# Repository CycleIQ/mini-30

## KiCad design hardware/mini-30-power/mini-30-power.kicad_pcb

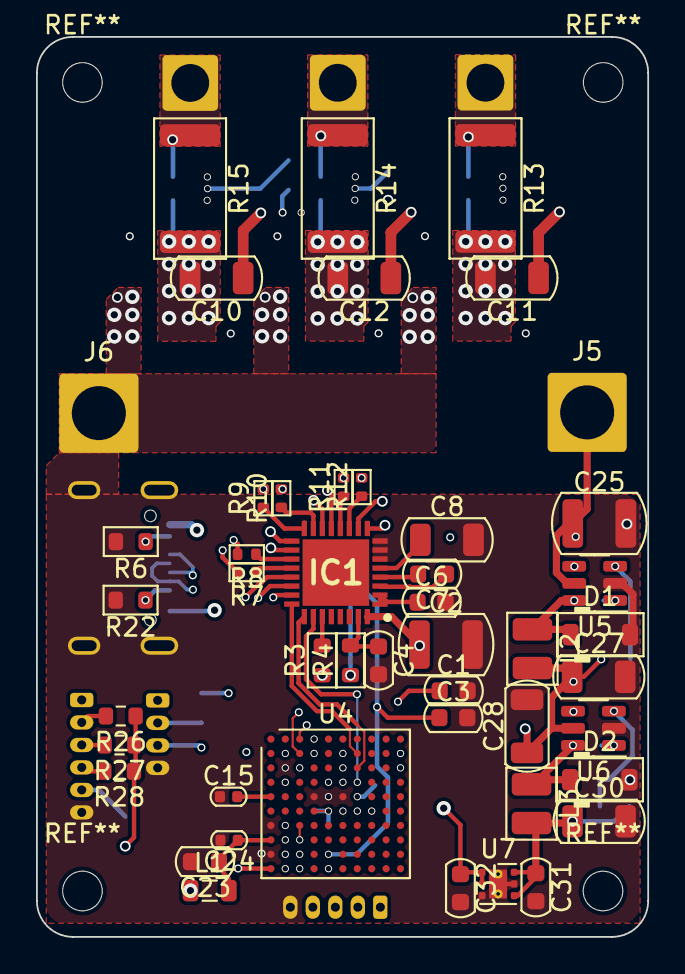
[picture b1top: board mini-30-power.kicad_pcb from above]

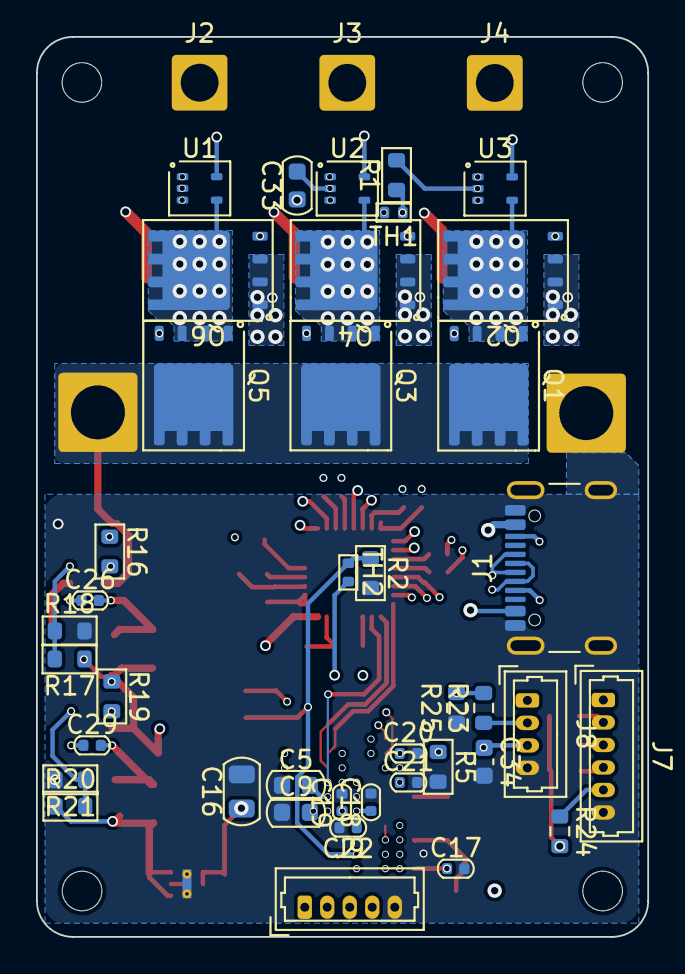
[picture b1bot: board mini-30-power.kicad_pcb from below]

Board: 6 copper layers, 34.0 x 50.0 mm, 90 parts (43 on the bottom side), 70 nets.

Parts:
C1, C3: C; C_0603_1608Metric
C2, C25: 10uF/100V; C_1210_3225Metric
C4: 1nF; C_0603_1608Metric
C5, C9: 2,2uF; C_0603_1608Metric
C6, C23, C33: 1uF; C_0603_1608Metric
C7: 10nF/25V; C_0603_1608Metric
C8, C27, C28, C30: 10uF/25V; C_1206_3216Metric
C10, C11, C12: 2.2uF; C_1206_3216Metric
C15, C17, C18, C19, C20, C21, C22, C24: 100nF; C_0402_1005Metric
C16: 4,7uF; C_0805_2012Metric
C26, C29: 100nF/16V; C_0402_1005Metric
C31, C32, C34: 2,2uF/10V; C_0603_1608Metric
D1, D2: 80V/1A; D_SOD-123
IC1: 6ED2742S01QXTMA1; QFN50P500X500X90-33N-D
J1: USB_C_Receptacle_USB2.0; USB_C_Receptacle_GCT_USB4105-xx-A_16P_TopMnt_Horizontal
J2: PHASE_A; SolderWire-1.5sqmm_1x01_D1.7mm_OD3mm
J3: PHASE_B; SolderWire-1.5sqmm_1x01_D1.7mm_OD3mm
J4: PHASE_C; SolderWire-1.5sqmm_1x01_D1.7mm_OD3mm
J5: BAT+; SolderWire-2.5sqmm_1x01_D2.4mm_OD4.4mm
J6: BAT-; SolderWire-2.5sqmm_1x01_D2.4mm_OD4.4mm
J7: CONN_HALL; Molex_PicoBlade_53047-0610_1x06_P1.25mm_Vertical
J8: CONN_PAS; Molex_PicoBlade_53047-0410_1x04_P1.25mm_Vertical
J9: CONN_DISPLAY; Molex_PicoBlade_53047-0510_1x05_P1.25mm_Vertical
L1: 27nH; L_0805_2012Metric
L2: 10uH; L_1008_2520Metric
L3: 6,8uH; L_1008_2520Metric
Q1, Q2, Q3, Q4, Q5, Q6: TPH1R306PL; Infineon_PG-TDSON-8
R1, R2, R5, R18, R21: 10k; R_0603_1608Metric
R3, R16, R19: 100k; R_0603_1608Metric
R4: 1M; R_0603_1608Metric
R6, R22: 5,1k; R_0603_1608Metric
R7, R8, R9, R10, R11, R12: 22; R_0402_1005Metric
R13, R14, R15: 1m; R_2512_6332Metric
R17: 147k; R_0603_1608Metric
R20: 54.9k; R_0603_1608Metric
R23: 33K; R_0603_1608Metric
R24, R25, R26, R27, R28: 10K; R_0603_1608Metric
TH1, TH2: Thermistor_NTC; R_0402_1005Metric
U1, U2, U3: SOT-353_SC-70-5
U4: STM32H753VIHx; TFBGA-100_8x8mm_Layout10x10_P0.8mm
U5, U6: LMR16006YQ5; SOT-23-6
U7: TLV76733DRVx; WSON-6-1EP_2x2mm_P0.65mm_EP1x1.6mm_ThermalVias

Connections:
+3.3V: C16.1, C17.1, C18.1, C19.1, C20.1, C21.1, C22.1, C32.1, C33.1, J9.1, L1.1, R3.1, R4.1, R24.2, R26.1, R27.1, R28.1, TH1.2, TH2.2, U1.3 (VS), U2.3 (VS), U3.3 (VS), U4.B2 (VBAT), U4.D2 (VDD), U4.F4 (VDDLDO), U4.F5 (VDD), U4.F6 (VDD33_USB), U4.F7 (PDR_ON), U4.K1 (VDD), U7.1 (OUT), U7.2 (SNS)
+3.3VA: C23.1, C24.1, L1.2, U4.H1 (VDDA)
+5V: C30.1, C31.1, J1.A4 (VBUS), J1.A9 (VBUS), J1.B4 (VBUS), J1.B9 (VBUS), J7.1, L3.2, R20.1, U7.4 (EN), U7.6 (IN)
+12V: C27.1, C28.1, J8.1, L2.2, R17.1, R19.1, U6.5 (VIN)
CS_A: U1.1 (OUT), U4.A3 (PE2)
CS_B: U2.1 (OUT), U4.B3 (PE3)
CS_C: U3.1 (OUT), U4.C3 (PE4)
DISPLAY_RX: J9.4, U4.A4 (PB9)
DISPLAY_TX: J9.3, U4.B4 (PB8)
GND: C1.2, C2.2, C3.2, C4.2, C5.1, C6.2, C8.2, C9.1, C15.1, C16.2, C17.2, C18.2, C19.2, C20.2, C21.2, C22.2, C23.2, C24.2, C25.2, C27.2, C28.2, C30.2, C31.2, C32.2, C33.2, C34.2, D1.2 (A), D2.2 (A), IC1.6 (VSS), IC1.7 (ITRIP), IC1.8 (COM), J1.A1 (GND), J1.A12 (GND), J1.B1 (GND), J1.B12 (GND), J1.S1 (SHIELD), J6.1, J7.6, J8.4, J9.5, Q2.1 (S), Q2.2 (S), Q2.3 (S), Q4.1 (S), Q4.2 (S), Q4.3 (S), Q6.1 (S), Q6.2 (S), Q6.3 (S), R1.2, R2.2, R5.2, R6.2, R18.2, R21.2, R22.2, R25.1, U1.2 (GND), U2.2 (GND), U3.2 (GND), U4.C2 (VSS), U4.E4 (VSS), U4.E5 (VSS), U4.E6 (VSS), U4.G1 (VSSA), U4.J1 (VSS), U5.2 (GND), U6.2 (GND), U7.3 (GND), U7.5 (GND), U7.7 (PAD)
HALL_A: J7.2, R26.2, U4.H2 (PA1)
HALL_B: J7.3, R27.2, U4.J2 (PA2)
HALL_C: J7.4, R28.2, U4.K2 (PA3)
HALL_S: J7.5, R24.1, U4.G3 (PA4), U4.H3 (PA5)
HIN_A: IC1.26 (HIN1), U4.D7 (PD4)
HIN_B: IC1.25 (HIN2), U4.C7 (PD3)
HIN_C: IC1.24 (HIN3), U4.B7 (PD2)
LIN_A: IC1.23 (LIN1), U4.B6 (PD5)
LIN_B: IC1.22 (LIN2), U4.C6 (PD6)
LIN_C: IC1.21 (LIN3), U4.D6 (PD7)
unnamed: C5.2, U4.E7 (VCAP)
unnamed: C9.2, U4.F8 (VCAP)
unnamed: C26.2, D1.1 (K), L2.1, U5.6 (SW)
unnamed: C29.2, D2.1 (K), L3.1, U6.6 (SW)
unnamed: C6.1, IC1.1 (BJT_DR), IC1.2 (VREG)
unnamed: C7.1, IC1.3 (CP1)
unnamed: C7.2, IC1.4 (CP2)
unnamed: IC1.11 (HO1), R12.1
unnamed: IC1.15 (HO2), R10.1
unnamed: IC1.19 (HO3), R8.1
unnamed: IC1.27 (ITRIP_CONF), R3.2
unnamed: IC1.12 (LO1), R11.1
unnamed: IC1.16 (LO2), R9.1
unnamed: IC1.20 (LO3), R7.1
unnamed: C4.1, IC1.31 (RFE), R4.2
unnamed: C11.1, IC1.9 (VB1)
unnamed: C12.1, IC1.13 (VB2)
unnamed: C10.1, IC1.17 (VB3)
unnamed: C8.1, IC1.5 (VCC)
unnamed: J1.A5 (CC1), R22.1
unnamed: J1.B5 (CC2), R6.1
unnamed: Q1.4 (G), R8.2
unnamed: Q2.4 (G), R7.2
unnamed: Q3.4 (G), R10.2
unnamed: Q4.4 (G), R9.2
unnamed: Q5.4 (G), R12.2
unnamed: Q6.4 (G), R11.2
unnamed: R5.1, U4.D5 (BOOT0)
unnamed: C15.2, U4.E1 (NRST)
unnamed: C26.1, U5.1 (CB)
unnamed: R17.2, R18.1, U5.3 (FB)
unnamed: R16.2, U5.4 (~SHDN)
unnamed: C29.1, U6.1 (CB)
unnamed: R20.2, R21.1, U6.3 (FB)
unnamed: R19.2, U6.4 (~SHDN)
PAS_SIGNAL: J8.2, R23.1
PAS_SIGNAL_LOW: R23.2, R25.2, U4.J3 (PA6)
PHASE_A: C11.2, IC1.10 (VS1), Q5.1 (S), Q5.2 (S), Q5.3 (S), Q6.5 (D), R13.2, U1.4 (IN+)
PHASE_A_CONN: J2.1, R13.1, U1.5 (IN-)
PHASE_B: C12.2, IC1.14 (VS2), Q3.1 (S), Q3.2 (S), Q3.3 (S), Q4.5 (D), R14.2, U2.4 (IN+)
PHASE_B_CONN: J3.1, R14.1, U2.5 (IN-)
PHASE_C: C10.2, IC1.18 (VS3), Q1.1 (S), Q1.2 (S), Q1.3 (S), Q2.5 (D), R15.2, U3.4 (IN+)
PHASE_C_CONN: J4.1, R15.1, U3.5 (IN-)
TH_HIGH: C3.1, R2.1, TH2.1, U4.J5 (PE8)
TH_LOW: C1.1, R1.1, TH1.1, U4.K5 (PE9)
TORQUE_OUTPUT: C34.1, J8.3, U4.K3 (PA7)
USB_D+: J1.A6 (D+), J1.B6 (D+), U4.B10 (PA12)
USB_D-: J1.A7 (D-), J1.B7 (D-), U4.C10 (PA11)
VCC: C2.1, C25.1, IC1.32 (VIN), J5.1, Q1.5 (D), Q3.5 (D), Q5.5 (D), R16.1, U5.5 (VIN)
WAKEUP: J9.2, U4.G2 (PA0)

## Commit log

2024-02-08 🎉 Initial commit
